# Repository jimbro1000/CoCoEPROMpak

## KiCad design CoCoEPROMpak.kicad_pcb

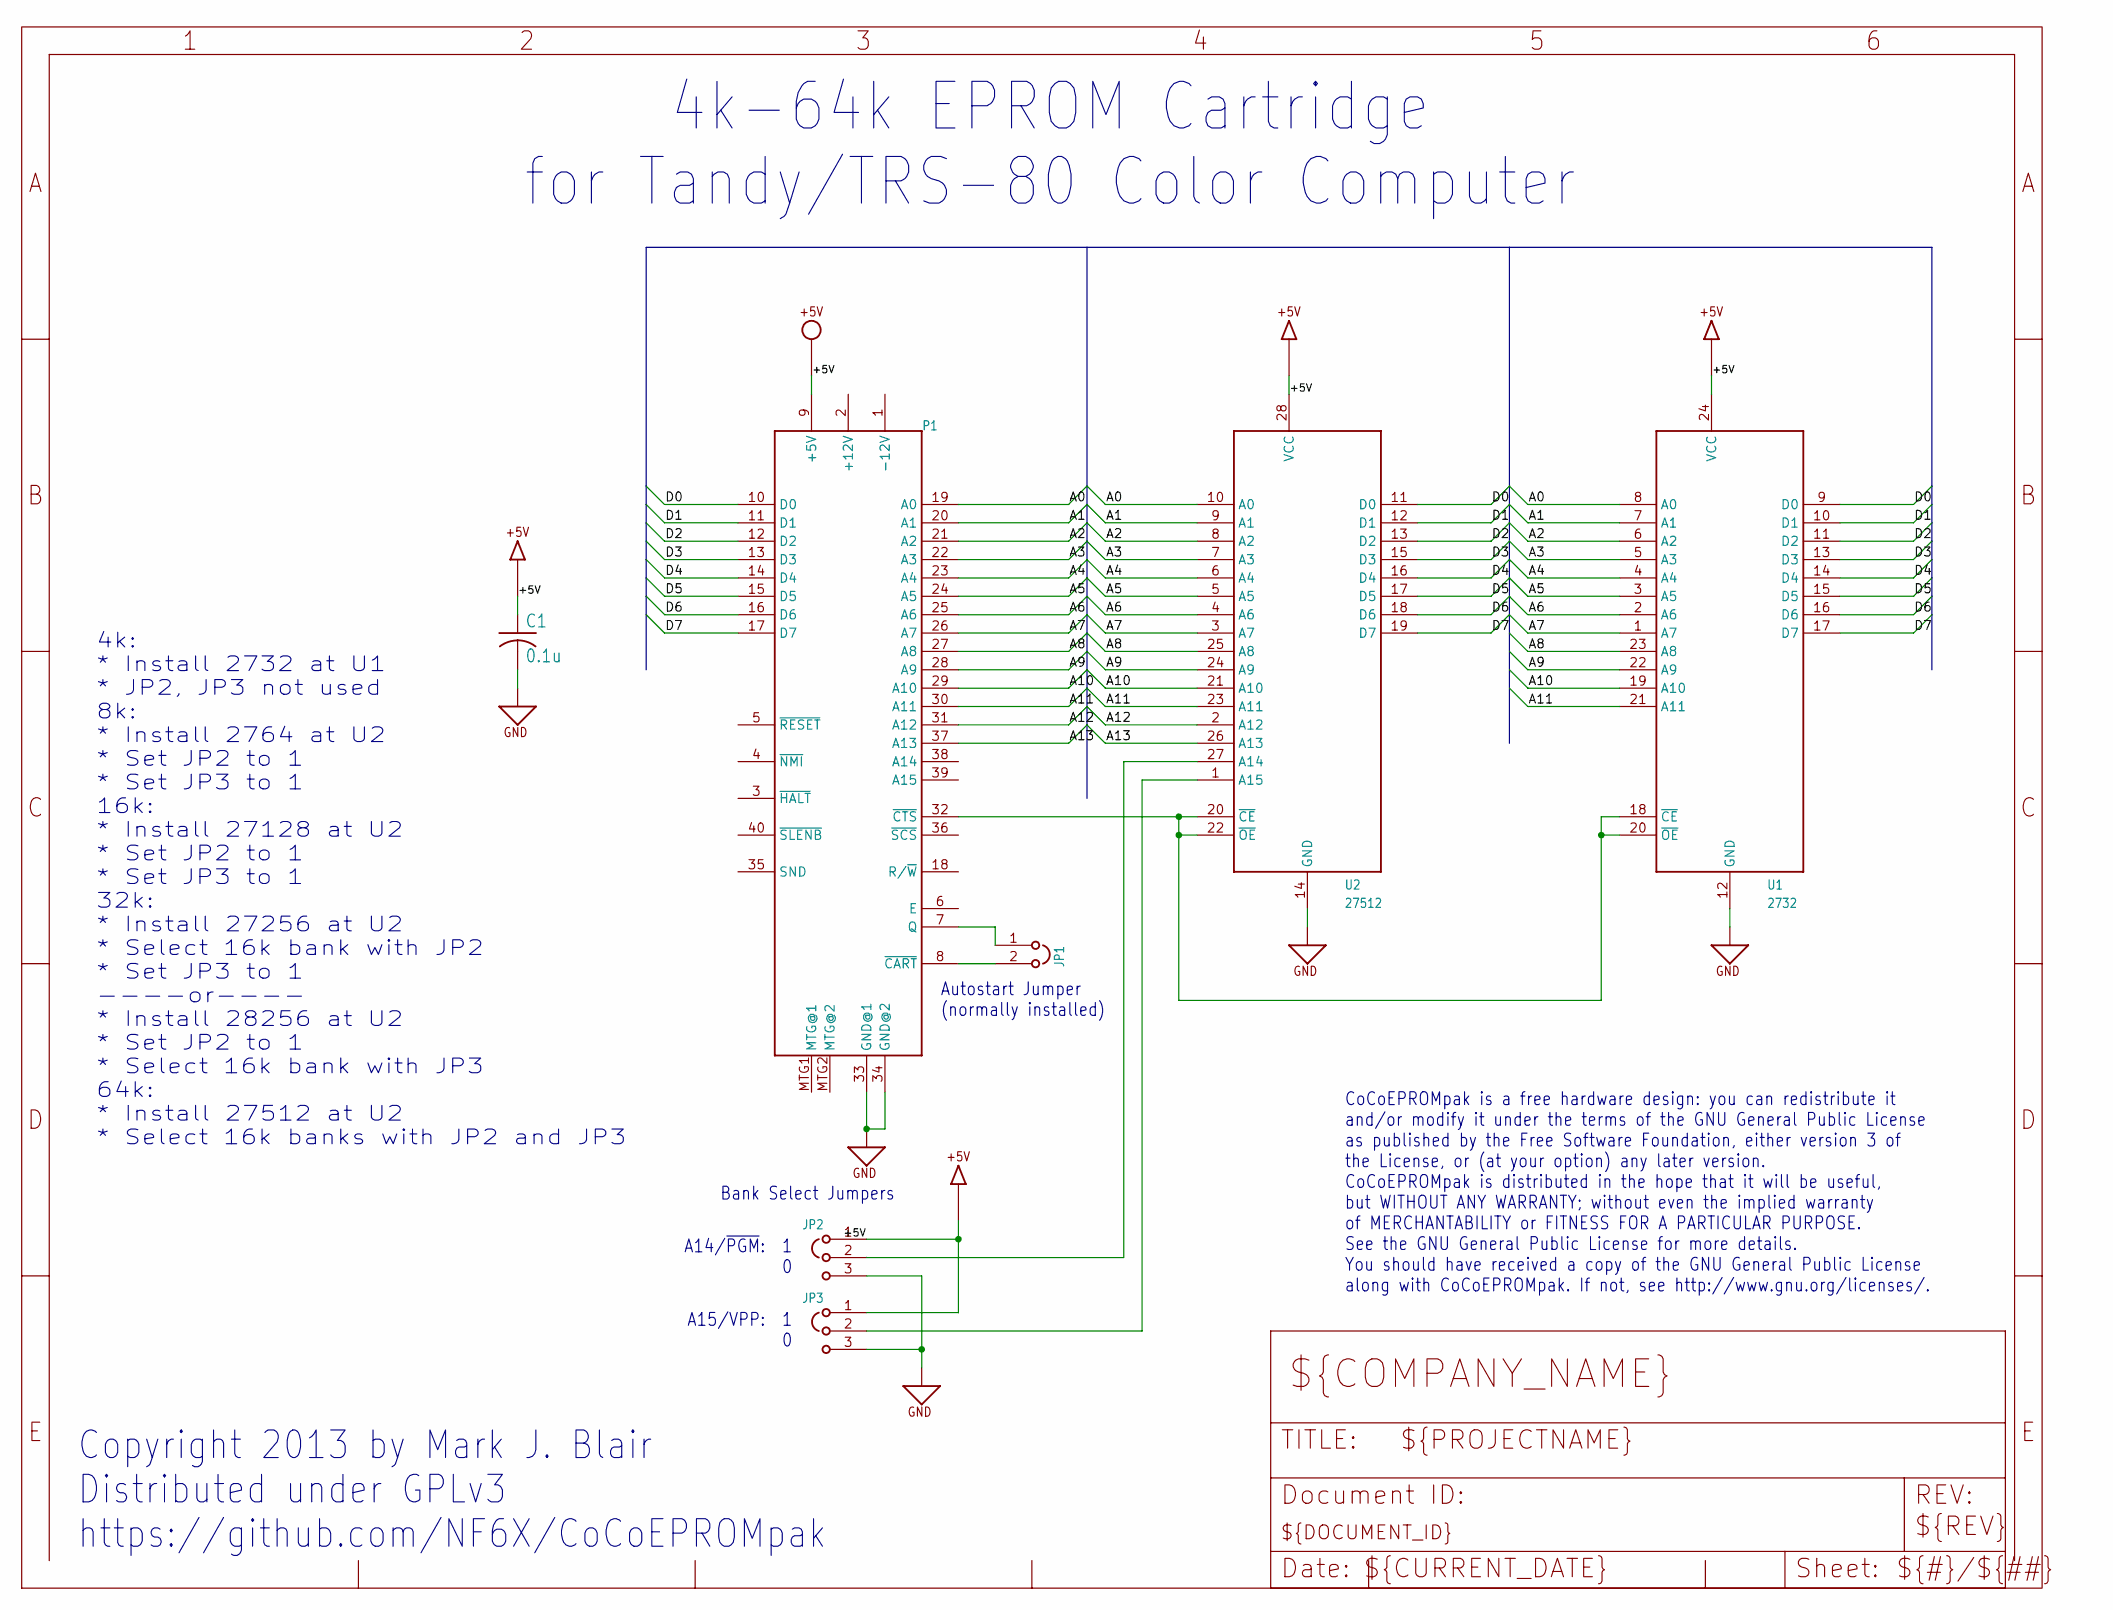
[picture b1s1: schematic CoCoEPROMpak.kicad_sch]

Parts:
C1: 0.1u; C_Disc_D5.0mm_W2.5mm_P5.00mm
JP1: JP2; PinHeader_1x02_P2.54mm_Vertical
JP2, JP3: JP3; PinHeader_1x03_P2.54mm_Vertical
P1: COCO-CART; COCO-CART-2.1X1.75
U1: 2732; DIL24
U2: 27512; DIP-28_W15.24mm

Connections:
+5V: C1.1, JP2.1, JP3.1, P1.9 (+5V), U1.24 (VCC), U2.28 (VCC)
/A0: P1.19 (A0), U1.8 (A0), U2.10 (A0)
/A1: P1.20 (A1), U1.7 (A1), U2.9 (A1)
/A2: P1.21 (A2), U1.6 (A2), U2.8 (A2)
/A3: P1.22 (A3), U1.5 (A3), U2.7 (A3)
/A4: P1.23 (A4), U1.4 (A4), U2.6 (A4)
/A5: P1.24 (A5), U1.3 (A5), U2.5 (A5)
/A6: P1.25 (A6), U1.2 (A6), U2.4 (A6)
/A7: P1.26 (A7), U1.1 (A7), U2.3 (A7)
/A8: P1.27 (A8), U1.23 (A8), U2.25 (A8)
/A9: P1.28 (A9), U1.22 (A9), U2.24 (A9)
/A10: P1.29 (A10), U1.19 (A10), U2.21 (A10)
/A11: P1.30 (A11), U1.21 (A11), U2.23 (A11)
/A12: P1.31 (A12), U2.2 (A12)
/A13: P1.37 (A13), U2.26 (A13)
/D0: P1.10 (D0), U1.9 (D0), U2.11 (D0)
/D1: P1.11 (D1), U1.10 (D1), U2.12 (D1)
/D2: P1.12 (D2), U1.11 (D2), U2.13 (D2)
/D3: P1.13 (D3), U1.13 (D3), U2.15 (D3)
/D4: P1.14 (D4), U1.14 (D4), U2.16 (D4)
/D5: P1.15 (D5), U1.15 (D5), U2.17 (D5)
/D6: P1.16 (D6), U1.16 (D6), U2.18 (D6)
/D7: P1.17 (D7), U1.17 (D7), U2.19 (D7)
GND: C1.2, JP2.3, JP3.3, P1.33 (GND@1), P1.34 (GND@2), U1.12 (GND), U2.14 (GND)
unnamed: JP1.1, P1.7 (Q)
unnamed: JP1.2, P1.8 (~CART)
unnamed: P1.32 (~CTS), U1.18 (~CE), U1.20 (~OE), U2.20 (~CE), U2.22 (~OE)
unnamed: JP2.2, U2.27 (A14)
unnamed: JP3.2, U2.1 (A15)

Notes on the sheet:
Bank Select Jumpers
4k-64k EPROM Cartridge for Tandy/TRS-80 Color Computer
Autostart Jumper (normally installed)
A14/~{PGM}: 1 0
A15/VPP: 1 0
Copyright 2013 by Mark J. Blair Distributed under GPLv3 https://github.com/NF6X/CoCoEPROMpak
CoCoEPROMpak is a free hardware design: you can redistribute it and/or modify it under the terms of the GNU General Public License as published by the Free Software Foundation, either version 3 of the License, or (at your option) any later version. CoCoEPROMpak is distributed in the hope that it wi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
4k: * Install 2732 at U1 * JP2, JP3 not used 8k: * Install 2764 at U2 * Set JP2 to 1 * Set JP3 to 1 16k: * Install 27128 at U2 * Set JP2 to 1 * Set JP3 to 1 32k: * Install 27256 at U2 * Select 16k bank with JP2 * Set JP3 to 1 ----or---- * Install 28256 at U2 * Set JP2 to 1 * Select 16k bank with JP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

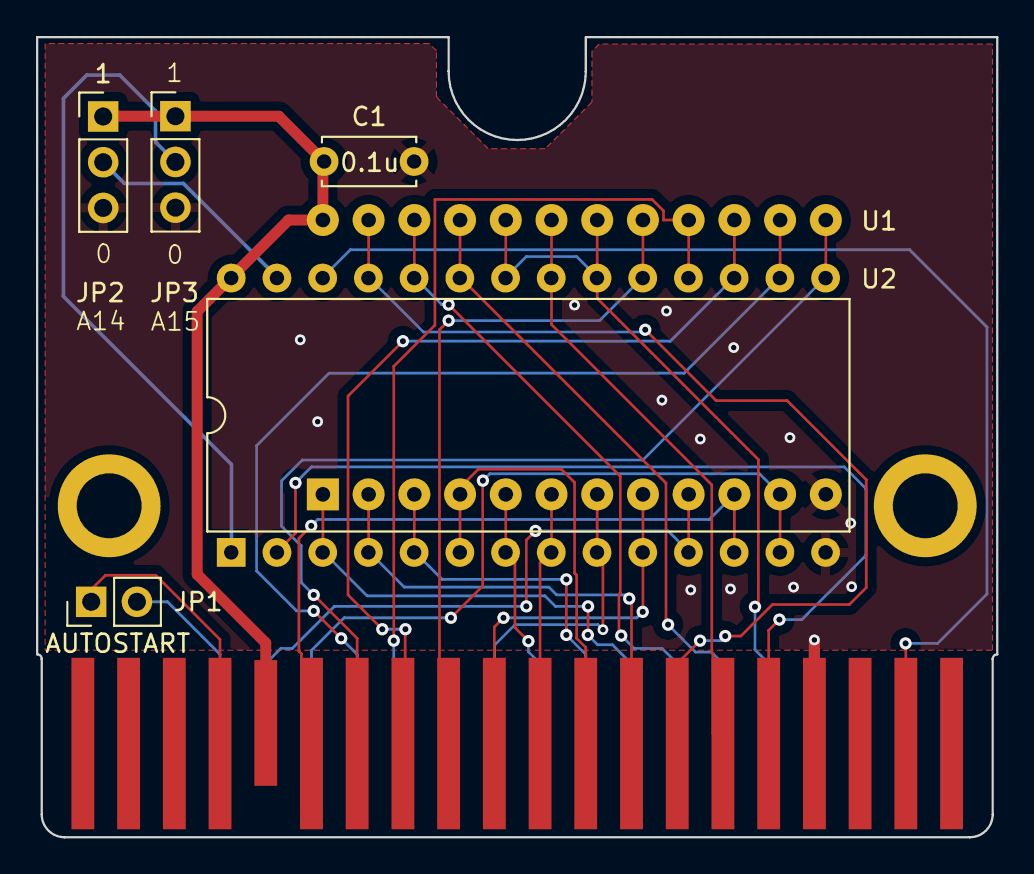
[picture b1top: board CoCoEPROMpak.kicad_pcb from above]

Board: 2 copper layers, 53.3 x 44.5 mm, 7 parts (0 on the bottom side), 29 nets.

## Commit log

2023-11-24 refresh project
2023-11-24 convert to kicad
2023-12-31 add renders

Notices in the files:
parts and their libraries:
Copyright 2013 Mark J. Blair_
